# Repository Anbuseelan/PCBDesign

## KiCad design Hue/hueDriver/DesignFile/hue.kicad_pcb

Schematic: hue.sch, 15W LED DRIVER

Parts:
C1, C3: 10uF/450V; CP_Radial_D10.0mm_P5.00mm
C2, C12: 10nF; C_0805_2012Metric_Pad1.33x1.40mm_HandSolder
C4: 22K; C_0805_2012Metric_Pad1.33x1.40mm_HandSolder
C5, C8: 1nF/1KV; C_0805_2012Metric_Pad1.33x1.40mm_HandSolder
C6: 4.7uF/50V; CP_Radial_D5.0mm_P2.50mm
C7: 1nF/Y1; Y1Capacitor
C9: 10uF; C_0805_2012Metric_Pad1.33x1.40mm_HandSolder
C10, C11: 330uF; CP_Radial_D8.0mm_P3.80mm
C13: 22uF/6.3V; C_0805_2012Metric_Pad1.33x1.40mm_HandSolder
C14: 0.1uF; C_0805_2012Metric_Pad1.33x1.40mm_HandSolder
D1: ABS8; Diode_Bridge_Diotec_ABS
D2, D3: DFLR1600-7; POWERDI-123
D4: 2SS100L-W; D_SOD-123F
D5: D_Small_ALT; D_SOD-323
F1: RST2; fuse_L7_W4_P5; MPN RST2
J1: OUT; 6PIN_conn
L1: 1mH; L_Radial_D7.5mm_P3.50mm_Fastron_07P
L2: 4.7uH; Inductor_Taiyo-Yuden_MD-4040
R1: 1.2R; R_0805_2012Metric
R2: 1.8R; R_0805_2012Metric
R3, R4: 2M; R_0805_2012Metric
R5: 10pF/16V; R_0805_2012Metric
R6: 150K; R_0805_2012Metric
R7: 10R; R_0805_2012Metric
R8: 47K; R_0805_2012Metric
R9: 30E; R_0805_2012Metric
R10: 4.7K; R_0805_2012Metric
R11: 49.9K; R_0805_2012Metric
R12: 16.2K; R_0805_2012Metric
RV1: Varistor; RV_Disc_D7_W3.4_P5
T1: EE19_8_Pin; EE19Horizondal
TP1: L; PAD
TP2: N; PAD
U1: AP3983; DIP-7_AP3983
U2: AP3211

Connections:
+3V3: C13.1, C14.1, J1.3, J1.4, L2.2, R11.1
+15V: C9.1, C10.1, C11.1, D4.1, J1.1, J1.2, R9.1, R10.1, U2.4, U2.5
/AC_L_IN: F1.1, TP1.1
/AC_N_IN: D1.3 (~~), RV1.2, TP2.1
/DC_BUS: C3.1, C5.1, L1.2, R3.1, R6.1, T1.1
/DRIAN: D3.2, T1.2, U1.5, U1.6
GND: C7.1, C9.2, C10.2, C11.2, C13.2, C14.2, D5.2, J1.5, J1.6, R10.2, R12.2, T1.5, U2.2
GNDPWR: C1.2, C2.2, C3.2, C4.2, C6.2, C7.2, D1.2 (-), R1.2, R2.2, R5.2, T1.4, U1.7
unnamed: C1.1, D1.1 (+), L1.1
unnamed: C2.1, U1.1
unnamed: C4.1, R5.1, R8.2, U1.2
unnamed: C5.2, D3.1, R6.2
unnamed: C6.1, R4.2, R7.2, U1.3
unnamed: C8.1, R9.2
unnamed: C8.2, D4.2, T1.8
unnamed: C12.1, D5.1, L2.1, U2.6
unnamed: C12.2, U2.1
unnamed: D1.4 (~~), F1.2, RV1.1
unnamed: D2.1, R7.1
unnamed: D2.2, R8.1, T1.3
unnamed: R1.1, R2.1, U1.4
unnamed: R3.2, R4.1
unnamed: R11.2, R12.1, U2.3

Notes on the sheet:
AC TO DC CONVERTER
DC TO DC CONVERTER
CONNECTOR

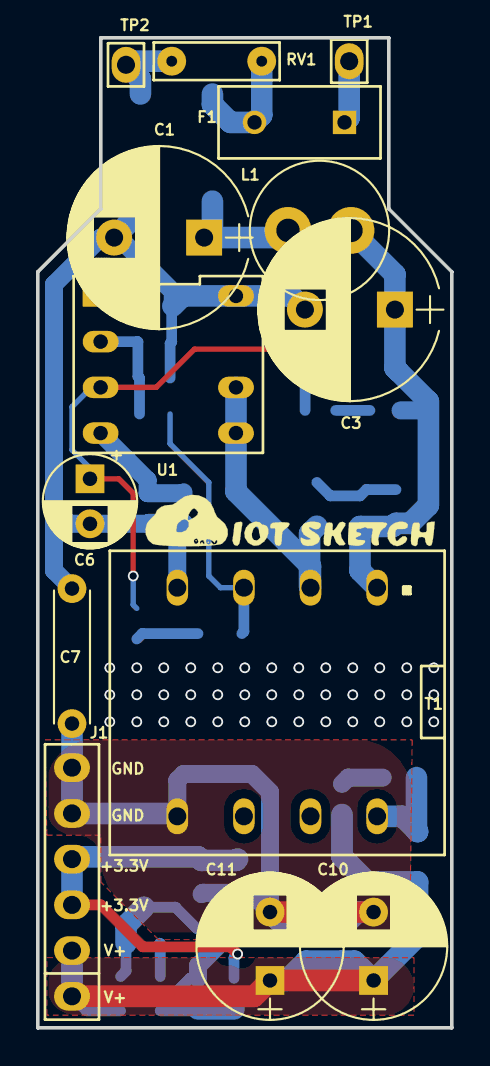
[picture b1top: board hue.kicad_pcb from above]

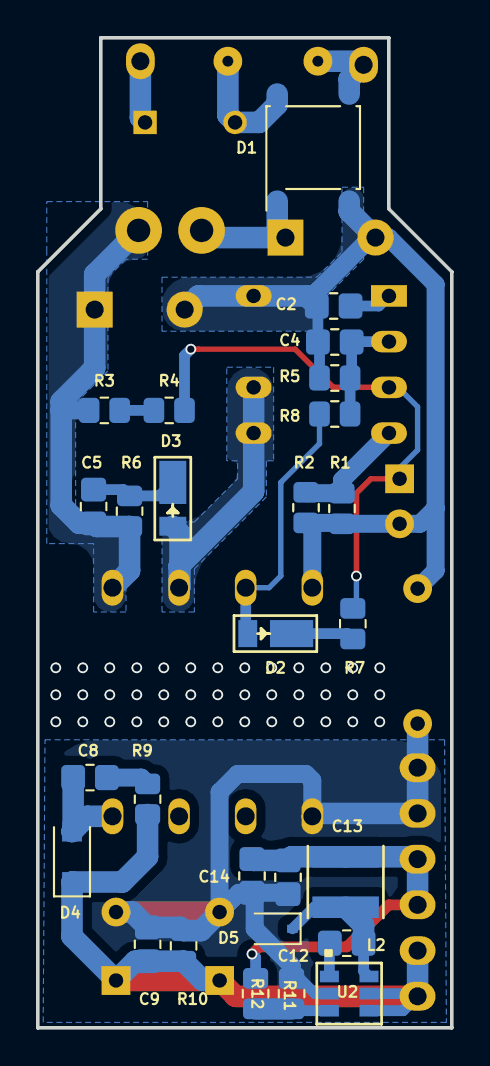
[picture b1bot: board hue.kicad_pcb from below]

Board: 2 copper layers, 23.0 x 55.0 mm, 41 parts (27 on the bottom side), 23 nets.

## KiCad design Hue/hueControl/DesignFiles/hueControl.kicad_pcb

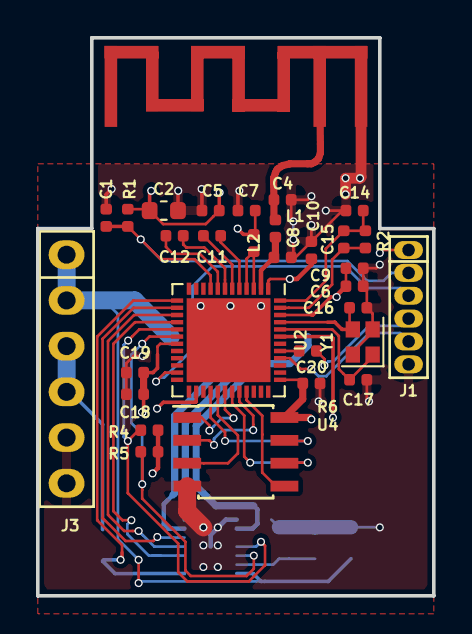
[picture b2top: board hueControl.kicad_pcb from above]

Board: 4 copper layers, 22.0 x 31.0 mm, 37 parts (0 on the bottom side), 35 nets.

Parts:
C1, C7, C10, C19: 0.1uF; C_0402_1005Metric
C2: 10uF; C_0603_1608Metric
C4: 2.0pF; C_0402_1005Metric
C5, C9, C18: 1uF; C_0402_1005Metric
C6: 100pF; C_0402_1005Metric
C8: 2.7pF; C_0402_1005Metric
C11, C12: 270pF; C_0402_1005Metric
C14: 10nF; C_0402_1005Metric
C15: 3.3nF; C_0402_1005Metric
C16, C17: 22pF; C_0402_1005Metric
C20: C_Small; C_0402_1005Metric
C21: 0.1uF; C_0603_1608Metric_Pad1.05x0.95mm_HandSolder
J1: DEBUG; 6Pin_1.27mm_conn
J2: OUTPUT; 4Pin_smd_conn
J3: INPUT; 6PIN_conn
L1: 2.7nH; L_0402_1005Metric
L2: 2.0nH; L_0402_1005Metric
R1: 10K; R_0402_1005Metric
R2: 20K; R_0402_1005Metric
R4, R5: 12K; R_0402_1005Metric
R6: 470R; R_0402_1005Metric
R7, R8, R9: 12K; R_0603_1608Metric_Pad1.05x0.95mm_HandSolder
U1: Antenna; PCB_Antenna_2_4_GHz_ESP32
U2: ESP32; QFN-48-1EP_6x6mm_P0.4mm_EP4.66x4.66mm
U3: AL1793; DFN-14-1EP_3x4mm_P0.5mm_EP1.7x3.3mm
U4: Flash; SOIC-8_3.9x4.9mm_P1.27mm
Y1: 40MHz; Crystal_SMD_2016-4Pin_2.0x1.6mm

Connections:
+3V3: C2.1, C5.1, C6.1, C7.1, C9.1, C10.1, C18.1, C19.1, C20.1, J1.1, J3.3, J3.4, L2.1, R1.2, R4.2, R5.2, R7.1, U2.1, U2.19, U2.26, U2.37, U2.43, U2.46, U4.8
+15V: C21.1, J2.1, J3.1, J3.2, U3.14
/Ant: C4.1, L1.1, U1.1
/B: U2.16, U3.3
/BLUE: J2.4, U3.9
/CHIP_PU: C1.1, J1.2, R1.1, U2.9
/EN_RGB: R7.2, U2.13, U3.1
/FAULTB: R5.1, U2.18, U3.12
/G: U2.15, U3.4
/GPIO0: J1.3, U2.23
/GREEN: J2.3, U3.7
/LEDPG: R4.1, U2.17, U3.11
/R: U2.14, U3.5
/RED: J2.2, U3.6
/SCK|CLK: U2.31, U4.6
/SCS|CMD: U2.30, U4.1
/SDI|SD1: U2.33, U4.5
/SDO|SD0: U2.32, U4.2
/SENSOR_VN: C12.2, U2.8
/SENSOR_VP: C11.1, U2.5
/SHD|SD2: U2.28, U4.7
/SWP|SD3: U2.29, U4.3
/U0RXD: J1.5, U2.40
/U0TXD: J1.4, R6.1
GND: C1.2, C2.2, C4.2, C5.2, C6.2, C7.2, C8.2, C9.2, C10.2, C14.2, C16.2, C17.2, C18.2, C19.2, C20.2, C21.2, J1.6, J3.5, J3.6, R8.1, R9.1, U1.2, U2.49, U3.8, U3.15, U4.4, Y1.2, Y1.4
unnamed: C8.1, L1.2, U2.2
unnamed: C11.2, U2.6
unnamed: C12.1, U2.7
unnamed: C14.1, C15.2, R2.2, U2.48
unnamed: C15.1, R2.1, U2.47
unnamed: C16.1, U2.45, Y1.3
unnamed: C17.1, U2.44, Y1.1
unnamed: L2.2, U2.3, U2.4
unnamed: R6.2, U2.41
unnamed: R8.2, R9.2, U3.13

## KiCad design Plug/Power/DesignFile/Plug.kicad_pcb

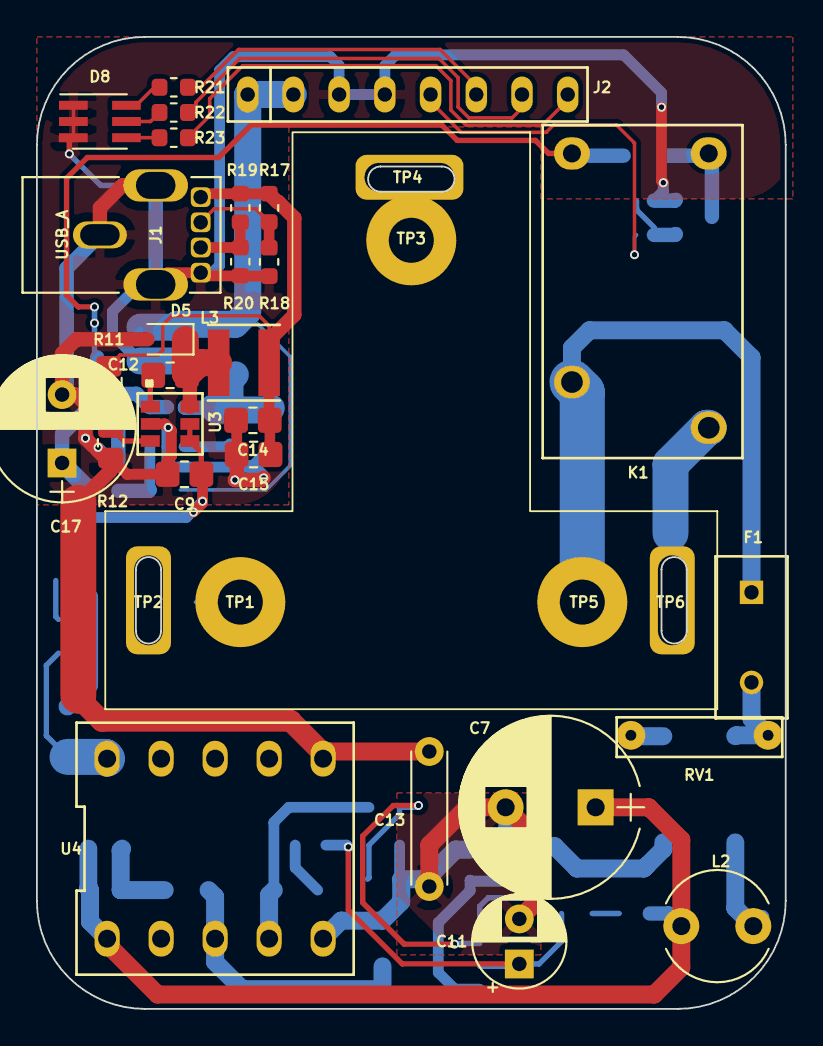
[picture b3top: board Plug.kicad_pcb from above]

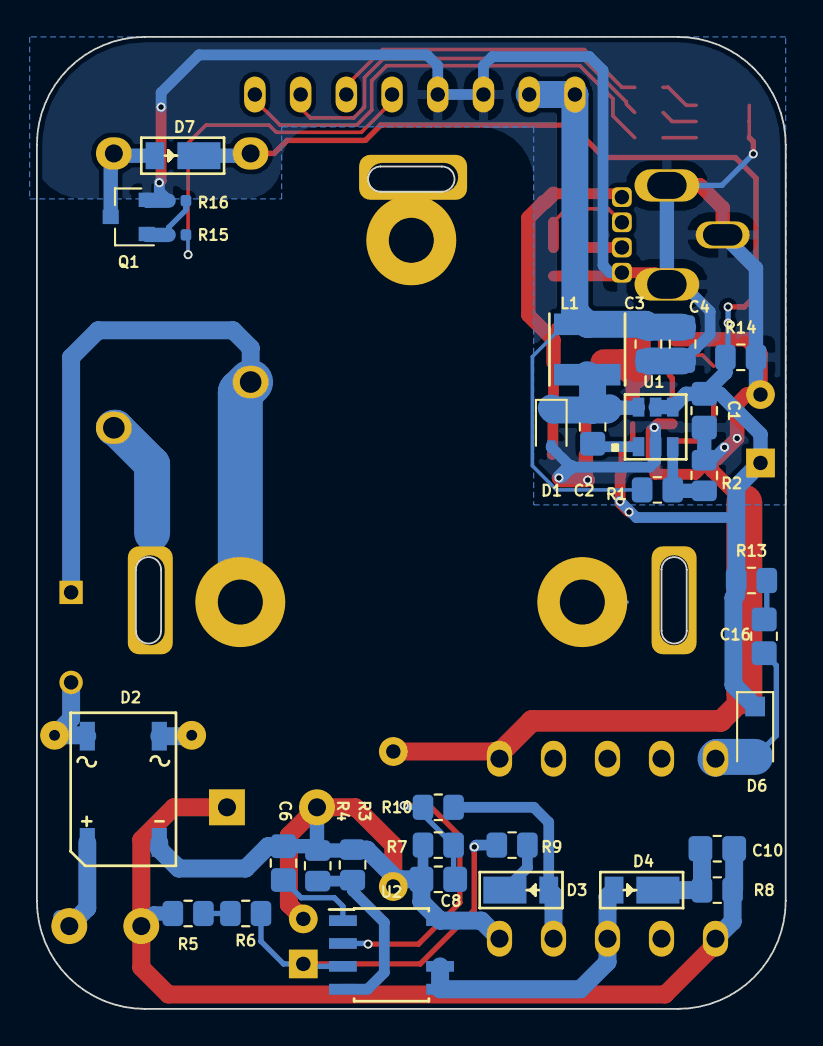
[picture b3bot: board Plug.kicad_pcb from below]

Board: 2 copper layers, 41.6 x 54.0 mm, 66 parts (32 on the bottom side), 41 nets.

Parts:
C1, C9: 10uF; C_0805_2012Metric_Pad1.33x1.40mm_HandSolder
C2, C6, C12: 10nF; C_0805_2012Metric_Pad1.33x1.40mm_HandSolder
C3, C14: 22uF/6.3V; C_0805_2012Metric_Pad1.33x1.40mm_HandSolder
C4, C15: 0.1uF; C_0805_2012Metric_Pad1.33x1.40mm_HandSolder
C7: 10uF/450V; CP_Radial_D10.0mm_P5.00mm
C8: 22K; C_0805_2012Metric_Pad1.33x1.40mm_HandSolder
C10, C16: 1nF/1KV; C_0805_2012Metric_Pad1.33x1.40mm_HandSolder
C11: 4.7uF/50V; CP_Radial_D5.0mm_P2.50mm
C13: 1nF/Y1; Y1Capacitor
C17: 680uF; CP_Radial_D8.0mm_P3.80mm
D1, D5: D_Small_ALT; D_SOD-323
D2: ABS8; MDB8S
D3, D4, D7: DFLR1600-7; POWERDI-123
D6: 2SS100L-W; D_SOD-123F
D8: LED_RGB; LED_Avago_PLCC6_3x2.8mm
F1: RST2; fuse_L7_W4_P5
J1: USB_A; USB_2.0_VER_SHORT
J2: I/O; 8Pin_Conn
K1: G5Q-1A; RELAY_4Pin
L1, L3: 4.7uH; Inductor_Taiyo-Yuden_MD-4040
L2: 1mH; L_Radial_D6.0mm_P4.00mm
Q1: Q_NMOS_GSD; SOT-23
R1, R11: 49.9K; R_0805_2012Metric
R2, R12: 16.2K; R_0805_2012Metric
R3: 1.2R; R_0805_2012Metric
R4: 1.8R; R_0805_2012Metric
R5, R6: 2M; R_0805_2012Metric
R7: 10pF/16V; R_0805_2012Metric
R8: 150K; R_0805_2012Metric
R9: 10R; R_0805_2012Metric
R10: 47K; R_0805_2012Metric
R13: 30E; R_0805_2012Metric
R14: 4.7K; R_0805_2012Metric
R15: 1K; R_0402_1005Metric
R16: 10K; R_0402_1005Metric
R17: 43K; R_0603_1608Metric
R18, R20: 51K; R_0603_1608Metric
R19: 75K; R_0603_1608Metric
R21, R22, R23: 220R; R_0603_1608Metric
RV1: Varistor; RV_Disc_D7_W3.4_P7.5
TP1: N1; MountingHole_2.5mm_Pad
TP2: N2; PAD_INPUT
TP3: E1; MountingHole_2.5mm_Pad
TP4: E2; PAD_INPUT
TP5: IN; MountingHole_2.5mm_Pad
TP6: OUT; PAD_INPUT
U1, U3: AP3211
U2: AP3983; AP3983R
U4: Transformer10Pin; EE16VERTICAL_SK

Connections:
+3V3: C3.1, C4.1, J2.1, J2.2, L1.2, R1.1
+5V: C14.1, C15.1, J1.1, L3.2, R11.1, R17.1, R19.1
+12V: C1.1, C9.1, C17.1, D6.1, D7.1, K1.2, R13.1, R14.1, U1.4, U1.5, U3.4, U3.5
/AC_L_IN: F1.1, K1.3, TP5.1
/AC_L_OUT: K1.4, TP6.1
/AC_N_IN: D2.3, RV1.2
/B: J2.8, R23.1
/DC_BUS: C7.1, C10.1, L2.2, R5.1, R8.1, U4.1
/DRIAN: D4.2, U2.5, U2.6, U4.3
/G: J2.7, R22.1
/R: J2.6, R21.1
/RELAY: J2.5, R15.2
GND: C1.2, C3.2, C4.2, C9.2, C13.1, C14.2, C15.2, C17.2, D1.2, D5.2, D8.1, D8.2, D8.3, J1.4, J1.SHEL, J2.3, J2.4, Q1.2, R2.2, R12.2, R14.2, R16.2, R18.2, R20.2, U1.2, U3.2, U4.6
GNDPWR: C6.2, C7.2, C8.2, C11.2, C13.2, D2.2, R3.2, R4.2, R7.2, U2.7, U4.5
unnamed: C2.1, D1.1, L1.1, U1.6
unnamed: C2.2, U1.1
unnamed: C6.1, U2.1
unnamed: C8.1, R7.1, R10.2, U2.2
unnamed: C10.2, D4.1, R8.2
unnamed: C11.1, R6.2, R9.2, U2.3
unnamed: C12.1, D5.1, L3.1, U3.6
unnamed: C12.2, U3.1
unnamed: C16.1, R13.2
unnamed: C16.2, D6.2, U4.10
unnamed: D2.1, L2.1
unnamed: D2.4, F1.2, RV1.1
unnamed: D3.1, R9.1
unnamed: D3.2, R10.1, U4.4
unnamed: D7.2, K1.1, Q1.3
unnamed: D8.4, R23.2
unnamed: D8.5, R22.2
unnamed: D8.6, R21.2
unnamed: J1.2, R17.2, R18.1
unnamed: J1.3, R19.2, R20.1
unnamed: Q1.1, R15.1, R16.1
unnamed: R1.2, R2.1, U1.3
unnamed: R3.1, R4.1, U2.4
unnamed: R5.2, R6.1
unnamed: R11.2, R12.1, U3.3
unnamed: TP1.1, TP2.1
unnamed: TP3.1, TP4.1

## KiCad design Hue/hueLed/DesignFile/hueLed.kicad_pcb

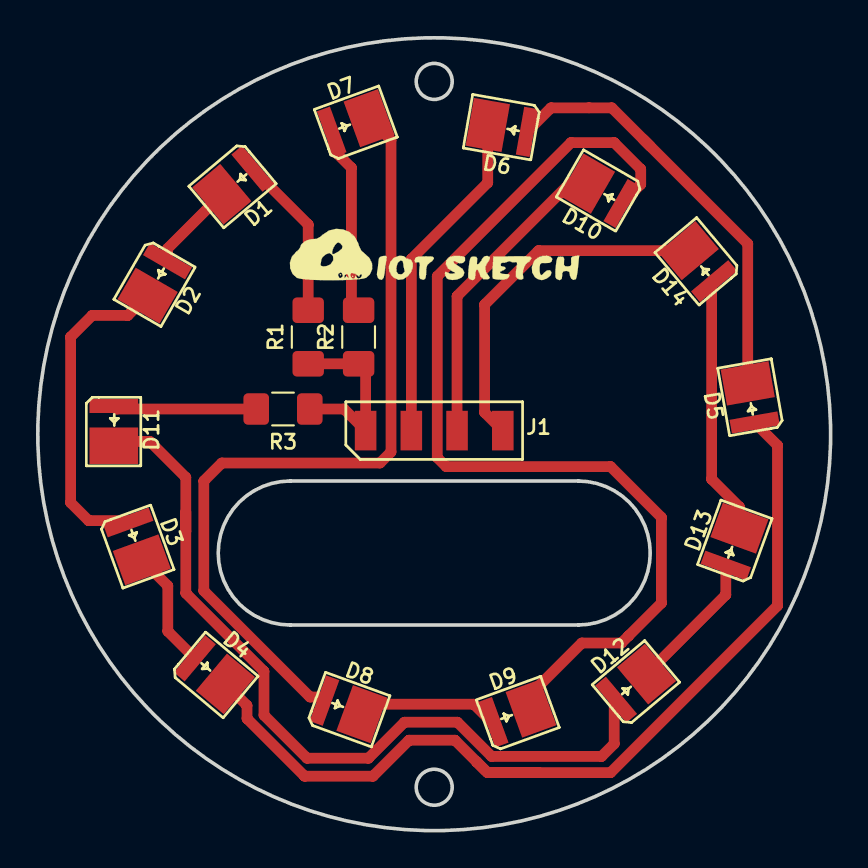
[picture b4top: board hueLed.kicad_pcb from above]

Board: 2 copper layers, 44.0 x 44.0 mm, 18 parts (0 on the bottom side), 18 nets.

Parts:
D1, D2, D3, D4, D5, D6: R; LED-3030_GBW
D7, D8, D9, D10: G; LED-3030_GBW
D11, D12, D13, D14: B; LED-3030_GBW
J1: Conn_01x04_Male; Conn-4
R1, R2, R3: 0R; R_1206_3216Metric_Pad1.42x1.75mm_HandSolder

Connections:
/BLUE: D14.1, J1.4
/GREEN: D10.1, J1.3
/RED: D6.1, J1.2
/V_driver: J1.1, R1.1, R2.1, R3.1
unnamed: D1.1, D2.2
unnamed: D1.2, R1.2
unnamed: D2.1, D3.2
unnamed: D3.1, D4.2
unnamed: D4.1, D5.2
unnamed: D5.1, D6.2
unnamed: D7.1, D8.2
unnamed: D7.2, R2.2
unnamed: D8.1, D9.2
unnamed: D9.1, D10.2
unnamed: D11.1, D12.2
unnamed: D11.2, R3.2
unnamed: D12.1, D13.2
unnamed: D13.1, D14.2

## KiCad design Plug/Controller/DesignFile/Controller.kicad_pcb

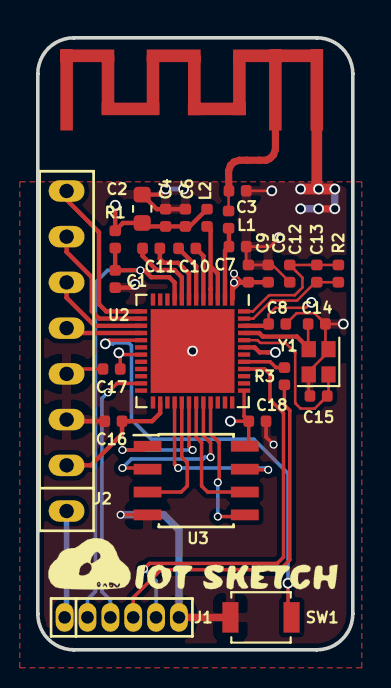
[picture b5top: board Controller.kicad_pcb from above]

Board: 4 copper layers, 17.5 x 34.0 mm, 30 parts (0 on the bottom side), 29 nets.

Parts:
C1, C6, C9, C17: 0.1uF; C_0402_1005Metric
C2: 10uF; C_0603_1608Metric
C3: 2.0pF; C_0402_1005Metric
C4, C8, C16: 1uF; C_0402_1005Metric
C5: 100pF; C_0402_1005Metric
C7: 2.7pF; C_0402_1005Metric
C10, C11: 270pF; C_0402_1005Metric
C12: 10nF; C_0402_1005Metric
C13: 3.3nF; C_0402_1005Metric
C14, C15: 22pF; C_0402_1005Metric
C18: C_Small; C_0402_1005Metric
J1: DEBUG; 6Pin_1.27mm_conn
J2: Conn_01x08_Male; 8Pin_Conn
L1: 2.7nH; L_0402_1005Metric
L2: 2.0nH; L_0402_1005Metric
R1: 10K; R_0402_1005Metric
R2: 20K; R_0402_1005Metric
R3: 470R; R_0402_1005Metric
SW1: SW_Push; SW_SPST_B3U-1000P
U1: Antenna; PCB_Antenna_2_4_GHz_ESP32
U2: ESP32; QFN-48-1EP_6x6mm_P0.4mm_EP4.66x4.66mm
U3: Flash; SOIC-8_3.9x4.9mm_P1.27mm
Y1: 40MHz; Crystal_SMD_2016-4Pin_2.0x1.6mm

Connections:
+3V3: C2.1, C4.1, C5.1, C6.1, C8.1, C9.1, C16.1, C17.1, C18.1, J1.1, J2.1, J2.2, L2.1, R1.2, U2.1, U2.19, U2.26, U2.37, U2.43, U2.46, U3.8
/Ant: C3.1, L1.1, U1.1
/B: J2.8, U2.13
/CHIP_PU: C1.1, J1.2, R1.1, U2.9
/G: J2.7, U2.14
/GPIO0: J1.3, U2.23
/GPIO14: SW1.2, U2.17
/R: J2.6, U2.15
/RELAY: J2.5, U2.16
/SCK|CLK: U2.31, U3.6
/SCS|CMD: U2.30, U3.1
/SDI|SD1: U2.33, U3.5
/SDO|SD0: U2.32, U3.2
/SENSOR_VN: C11.2, U2.8
/SENSOR_VP: C10.1, U2.5
/SHD|SD2: U2.28, U3.7
/SWP|SD3: U2.29, U3.3
/U0RXD: J1.5, U2.40
/U0TXD: J1.4, R3.1
GND: C1.2, C2.2, C3.2, C4.2, C5.2, C6.2, C7.2, C8.2, C9.2, C12.2, C14.2, C15.2, C16.2, C17.2, C18.2, J1.6, J2.3, J2.4, SW1.1, U1.2, U2.49, U3.4, Y1.2, Y1.4
unnamed: C7.1, L1.2, U2.2
unnamed: C10.2, U2.6
unnamed: C11.1, U2.7
unnamed: C12.1, C13.2, R2.2, U2.48
unnamed: C13.1, R2.1, U2.47
unnamed: C14.1, U2.45, Y1.3
unnamed: C15.1, U2.44, Y1.1
unnamed: L2.2, U2.3, U2.4
unnamed: R3.2, U2.41

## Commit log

2018-09-11 hardware and PCB Design files
